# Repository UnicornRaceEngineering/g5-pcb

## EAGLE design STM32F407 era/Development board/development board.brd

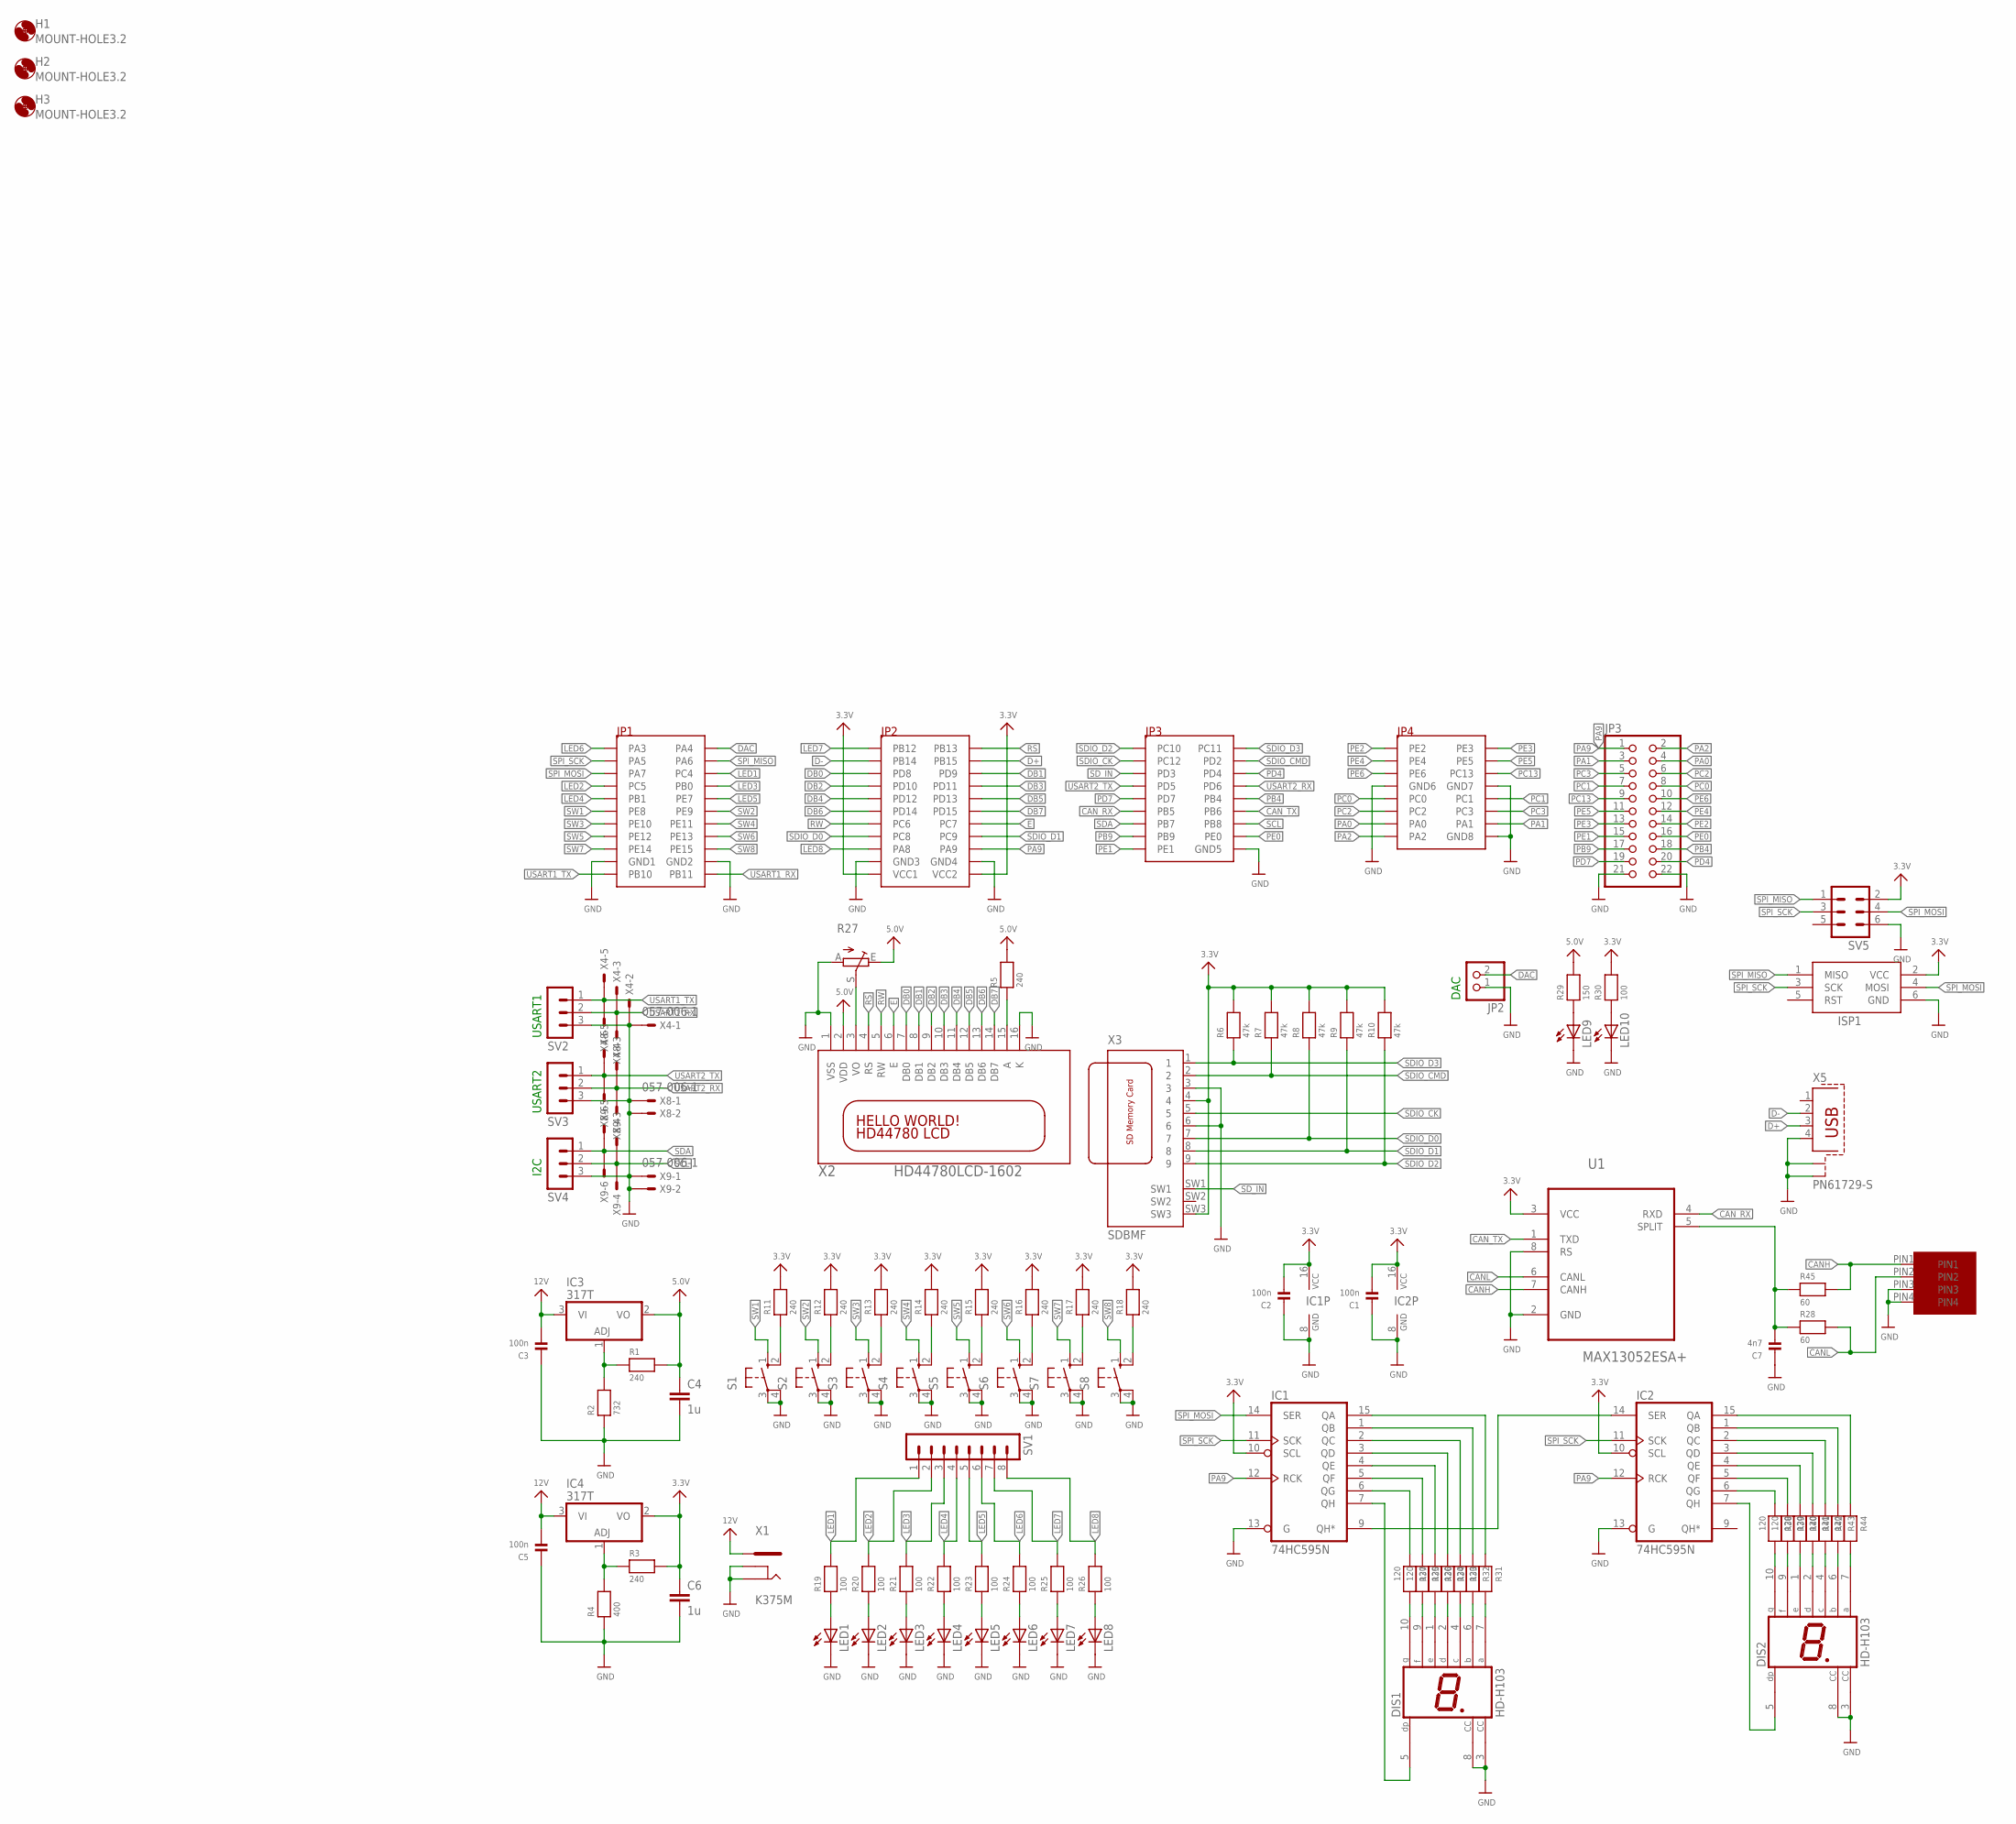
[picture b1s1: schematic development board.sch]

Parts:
C1, C2, C3, C5: 100n; _0603
C4, C6: 1u; C050-035X075
C7: 4n7; _0603
DIS1, DIS2: HD-H103; HDSP-M
H1, H2, H3: MOUNT-HOLE3.2; 3,2
IC1, IC2: 74HC595N; DIL16
IC3, IC4: 317T; TO220H
ISP1: AVRISP-BOX
JP2: HEADER-1X2ROUND; 1X02_ROUND
JP3: PINHD-2X11; 2X11
LED1, LED2, LED3, LED4, LED5, LED6, LED7, LED8: LED5MM
LED9, LED10: LED3MM
R1, R3, R5, R11, R12, R13, R14, R15, R16, R17, R18: 240; _0603
R2: 732; _0603
R4: 400; _0603
R6, R7, R8, R9, R10: 47k; _0603
R19, R20, R21, R22, R23, R24, R25, R26, R30: 100; _0603
R27: TRIM_EU-RJ9W; RJ9W
R28, R45: 60; _0603
R29: 150; _0603
R31, R32, R33, R34, R35, R36, R37, R38, R39, R40, R41, R42, R43, R44: 120; _0603
S1, S2, S3, S4, S5, S6, S7, S8: 10-XX; B3F-10XX
SV1: MA08-1
SV2, SV3, SV4: MA03-1
SV5: MA03-2
U1: MAX13052ESA+; SOIC127P600X175-8N
U$1: CPU-BOARD; CPU-BOARD-JP1
U$57: MICROFIT4; MICROFIT4SOCK
X1: K375M
X2: HD44780LCD-1602; LCD1602
X3: SDBMF; SDBMF-009XXBXX2
X4, X8, X9: 057-006-1
X5: PN61729-S

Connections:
3.3V: C1.2, C2.2, C6.1, IC1.10 (SCL), IC1.16 (VCC), IC2.10 (SCL), IC2.16 (VCC), IC4.2 (VO), ISP1.2 (VCC), R3.2, R6.2, R7.2, R8.2, R9.2, R10.2, R11.2, R12.2, R13.2, R14.2, R15.2, R16.2, R17.2, R18.2, R30.2, SV5.2, U1.3 (VCC), U$1.P$43 (VCC1), U$1.P$44 (VCC2), X3.4, X3.SW3
5.0V: C4.1, IC3.2 (VO), R1.2, R5.2, R27.E, R29.2, X2.2 (VDD)
12V: C3.2, C5.2, IC3.3 (VI), IC4.3 (VI), X1.1
CANH: R45.2, U1.7 (CANH), U$57.PIN1
CANL: R28.2, U1.6 (CANL), U$57.PIN2
CAN_RX: U1.4 (RXD), U$1.P$55 (PB5)
CAN_TX: U1.1 (TXD), U$1.P$56 (PB6)
D+: U$1.P$26 (PB15), X5.3
D-: U$1.P$25 (PB14), X5.2
DAC: JP2.2, U$1.P$2 (PA4)
DB0: U$1.P$27 (PD8), X2.7 (DB0)
DB1: U$1.P$28 (PD9), X2.8 (DB1)
DB2: U$1.P$29 (PD10), X2.9 (DB2)
DB3: U$1.P$30 (PD11), X2.10 (DB3)
DB4: U$1.P$31 (PD12), X2.11 (DB4)
DB5: U$1.P$32 (PD13), X2.12 (DB5)
DB6: U$1.P$33 (PD14), X2.13 (DB6)
DB7: U$1.P$34 (PD15), X2.14 (DB7)
E: U$1.P$36 (PC7), X2.6 (E)
GND: C1.1, C2.1, C3.1, C4.2, C5.1, C6.2, C7.1, DIS1.3 (CC), DIS1.8 (CC), DIS2.3 (CC), DIS2.8 (CC), IC1.8 (GND), IC1.13 (G), IC2.8 (GND), IC2.13 (G), ISP1.6 (GND), JP2.1, JP3.21, JP3.22, LED1.K (C), LED2.K (C), LED3.K (C), LED4.K (C), LED5.K (C), LED6.K (C), LED7.K (C), LED8.K (C), LED9.K (C), LED10.K (C), R2.1, R4.1, R27.A, S1.3, S1.4 (P1), S2.3, S2.4 (P1), S3.3, S3.4 (P1), S4.3, S4.4 (P1), S5.3, S5.4 (P1), S6.3, S6.4 (P1), S7.3, S7.4 (P1), S8.3, S8.4 (P1), SV2.3, SV3.3, SV4.3, SV5.6, U1.2 (GND), U1.8 (RS), U$1.P$21 (GND1), U$1.P$22 (GND2), U$1.P$41 (GND3), U$1.P$42 (GND4), U$1.P$62 (GND5), U$1.P$69 (GND6), U$1.P$70 (GND7), U$1.P$78 (GND8), U$57.PIN3, U$57.PIN4, X1.2, X1.3, X2.1 (VSS), X2.16 (K), X3.3, X3.6, X4.1, X4.2, X5.4, X5.S1, X5.S2, X8.1, X8.2, X9.1, X9.2
LED1: R19.2, SV1.1, U$1.P$6 (PC4)
LED2: R20.2, SV1.2, U$1.P$7 (PC5)
LED3: R21.2, SV1.3, U$1.P$8 (PB0)
LED4: R22.2, SV1.4, U$1.P$9 (PB1)
LED5: R23.2, SV1.5, U$1.P$10 (PE7)
LED6: R24.2, SV1.6, U$1.P$1 (PA3)
LED7: R25.2, SV1.7, U$1.P$23 (PB12)
LED8: R26.2, SV1.8, U$1.P$39 (PA8)
unnamed: DIS2.5 (DP), IC2.7 (QH)
unnamed: IC2.6 (QG), R38.1
unnamed: IC2.5 (QF), R39.1
unnamed: IC2.4 (QE), R40.1
unnamed: IC2.3 (QD), R41.1
unnamed: IC2.2 (QC), R42.1
unnamed: IC2.1 (QB), R43.1
unnamed: IC2.15 (QA), R44.1
unnamed: IC1.9 (QH*), IC2.14 (SER)
unnamed: DIS1.5 (DP), IC1.7 (QH)
unnamed: IC1.6 (QG), R37.1
unnamed: IC1.5 (QF), R35.1
unnamed: IC1.4 (QE), R36.1
unnamed: IC1.3 (QD), R34.1
unnamed: IC1.2 (QC), R33.1
unnamed: IC1.1 (QB), R32.1
unnamed: IC1.15 (QA), R31.1
unnamed: R5.1, X2.15 (A)
unnamed: R11.1, S1.2 (S1)
unnamed: LED10.A, R30.1
unnamed: R12.1, S2.2 (S1)
unnamed: IC3.1 (ADJ), R1.1, R2.2
unnamed: R13.1, S3.2 (S1)
unnamed: IC4.1 (ADJ), R3.1, R4.2
unnamed: R14.1, S4.2 (S1)
unnamed: R15.1, S5.2 (S1)
unnamed: R16.1, S6.2 (S1)
unnamed: R17.1, S7.2 (S1)
unnamed: R18.1, S8.2 (S1)
unnamed: LED1.A, R19.1
unnamed: LED9.A, R29.1
unnamed: LED2.A, R20.1
unnamed: LED3.A, R21.1
unnamed: LED4.A, R22.1
unnamed: LED5.A, R23.1
unnamed: LED6.A, R24.1
unnamed: LED7.A, R25.1
unnamed: LED8.A, R26.1
unnamed: DIS1.7 (A), R31.2
unnamed: DIS1.6 (B), R32.2
unnamed: DIS1.4 (C), R33.2
unnamed: DIS1.2 (D), R34.2
unnamed: DIS1.9 (F), R35.2
unnamed: DIS1.1 (E), R36.2
unnamed: DIS1.10 (G), R37.2
unnamed: DIS2.10 (G), R38.2
unnamed: DIS2.9 (F), R39.2
unnamed: DIS2.1 (E), R40.2
unnamed: DIS2.2 (D), R41.2
unnamed: DIS2.4 (C), R42.2
unnamed: DIS2.6 (B), R43.2
unnamed: DIS2.7 (A), R44.2
unnamed: C7.2, R28.1, R45.1, U1.5 (SPLIT)
PA0: JP3.4, U$1.P$75 (PA0)
PA1: JP3.3, U$1.P$76 (PA1)
PA2: JP3.2, U$1.P$77 (PA2)
PA9: IC1.12 (RCK), IC2.12 (RCK), JP3.1, U$1.P$40 (PA9)
PB4: JP3.18, U$1.P$54 (PB4)
PB9: JP3.17, U$1.P$59 (PB9)
PC0: JP3.8, U$1.P$71 (PC0)
PC1: JP3.7, U$1.P$72 (PC1)
PC2: JP3.6, U$1.P$73 (PC2)
PC3: JP3.5, U$1.P$74 (PC3)
PC13: JP3.9, U$1.P$68 (PC13)
PD4: JP3.20, U$1.P$50 (PD4)
PD7: JP3.19, U$1.P$53 (PD7)
PE0: JP3.16, U$1.P$60 (PE0)
PE1: JP3.15, U$1.P$61 (PE1)
PE2: JP3.14, U$1.P$63 (PE2)
PE3: JP3.13, U$1.P$64 (PE3)
PE4: JP3.12, U$1.P$65 (PE4)
PE5: JP3.11, U$1.P$66 (PE5)
PE6: JP3.10, U$1.P$67 (PE6)
RS: U$1.P$24 (PB13), X2.4 (RS)
RW: U$1.P$35 (PC6), X2.5 (RW)
SCL: SV4.2, U$1.P$58 (PB8), X9.3, X9.4
SDA: SV4.1, U$1.P$57 (PB7), X9.5, X9.6
SDIO_CK: U$1.P$47 (PC12), X3.5
SDIO_CMD: R7.1, U$1.P$48 (PD2), X3.2
SDIO_D0: R8.1, U$1.P$37 (PC8), X3.7
SDIO_D1: R9.1, U$1.P$38 (PC9), X3.8
SDIO_D2: R10.1, U$1.P$45 (PC10), X3.9
SDIO_D3: R6.1, U$1.P$46 (PC11), X3.1
SD_IN: U$1.P$49 (PD3), X3.SW1
SPI_MISO: ISP1.1 (MISO), SV5.1, U$1.P$4 (PA6)
SPI_MOSI: IC1.14 (SER), ISP1.4 (MOSI), SV5.4, U$1.P$5 (PA7)
SPI_SCK: IC1.11 (SCK), IC2.11 (SCK), ISP1.3 (SCK), SV5.3, U$1.P$3 (PA5)
SW1: S1.1 (S), U$1.P$11 (PE8)
SW2: S2.1 (S), U$1.P$12 (PE9)
SW3: S3.1 (S), U$1.P$13 (PE10)
SW4: S4.1 (S), U$1.P$14 (PE11)
SW5: S5.1 (S), U$1.P$15 (PE12)
SW6: S6.1 (S), U$1.P$16 (PE13)
SW7: S7.1 (S), U$1.P$17 (PE14)
SW8: S8.1 (S), U$1.P$18 (PE15)
USART1_RX: SV2.2, U$1.P$20 (PB11), X4.3, X4.4
USART1_TX: SV2.1, U$1.P$19 (PB10), X4.5, X4.6
USART2_RX: SV3.2, U$1.P$52 (PD6), X8.3, X8.4
USART2_TX: SV3.1, U$1.P$51 (PD5), X8.5, X8.6
VO: R27.S, X2.3 (VO)

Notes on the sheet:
USART1
USART2
I2C
DAC

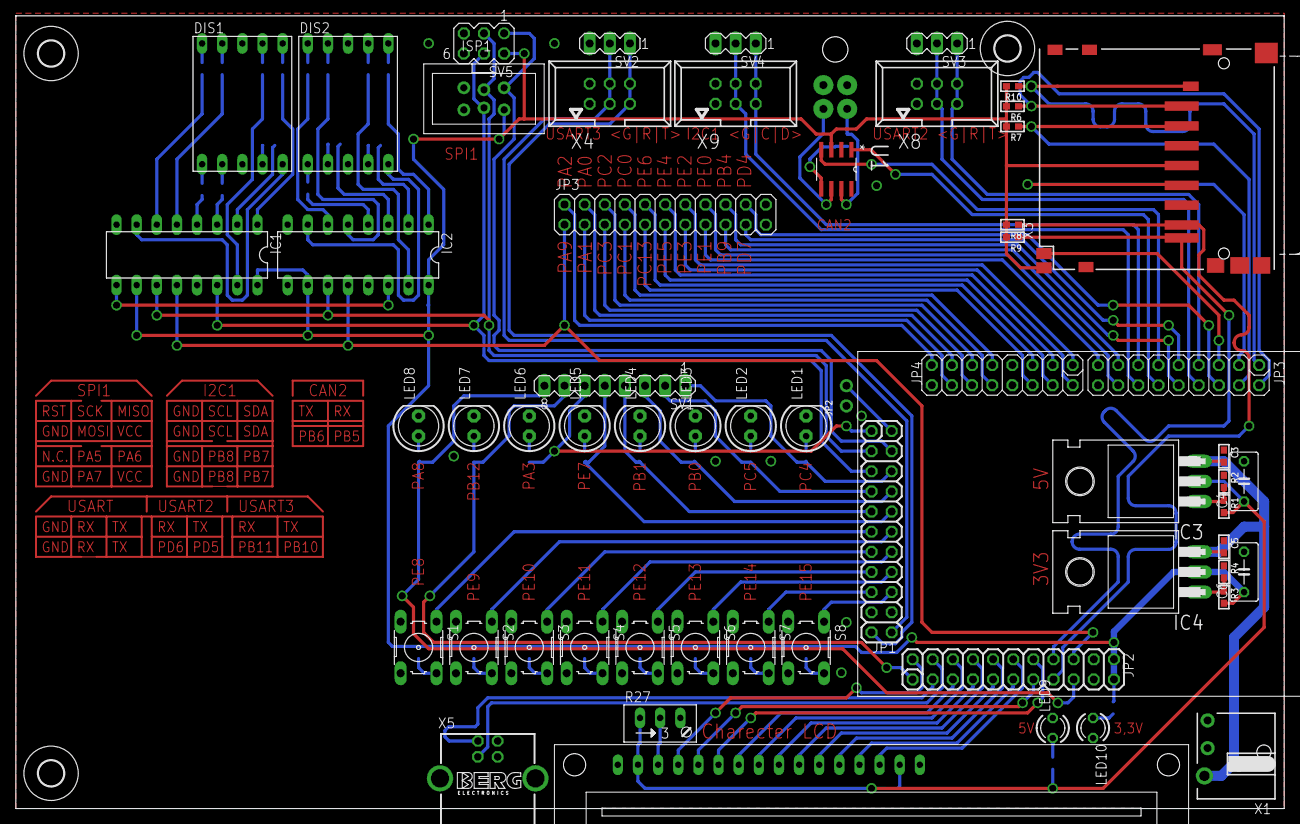
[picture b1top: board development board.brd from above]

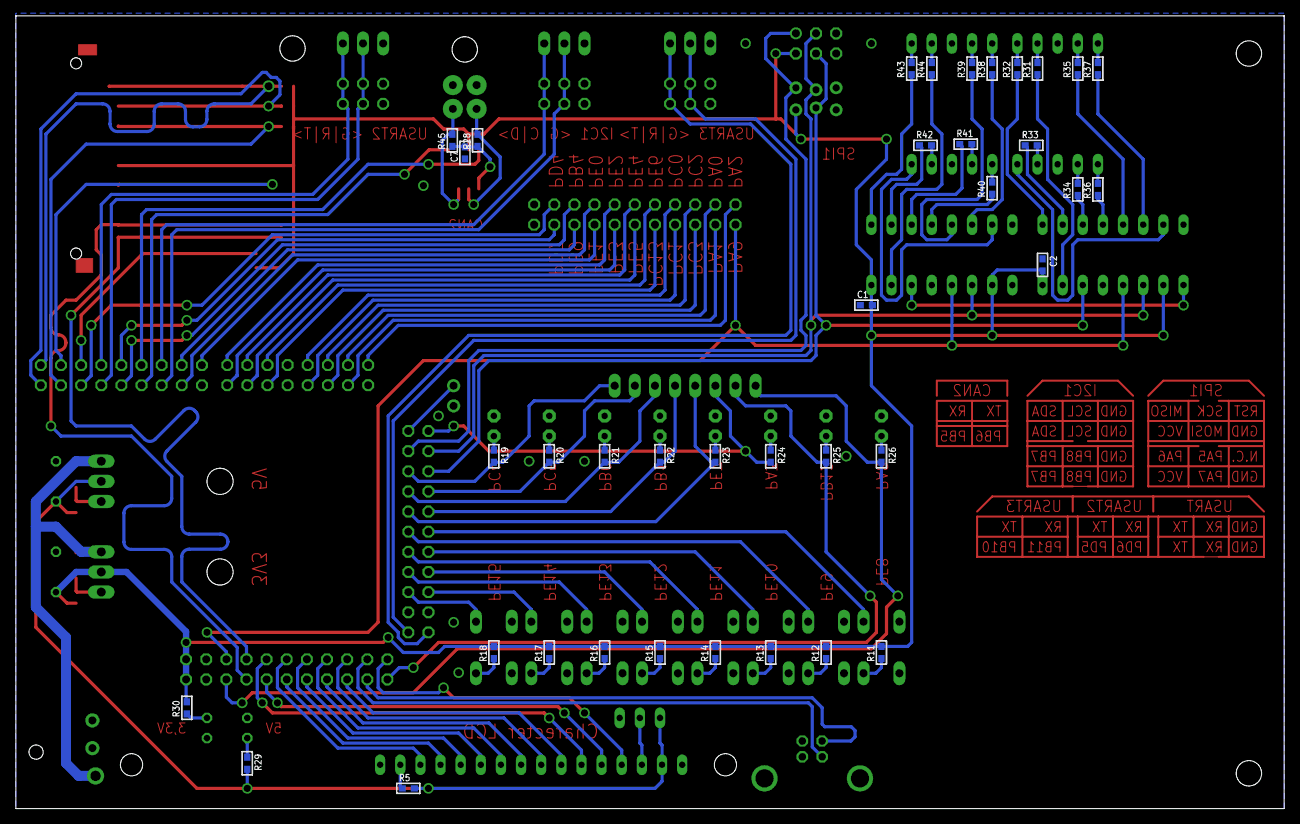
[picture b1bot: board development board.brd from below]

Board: 2 copper layers, 160.0 x 100.0 mm, 97 parts (38 on the bottom side), 128 nets.

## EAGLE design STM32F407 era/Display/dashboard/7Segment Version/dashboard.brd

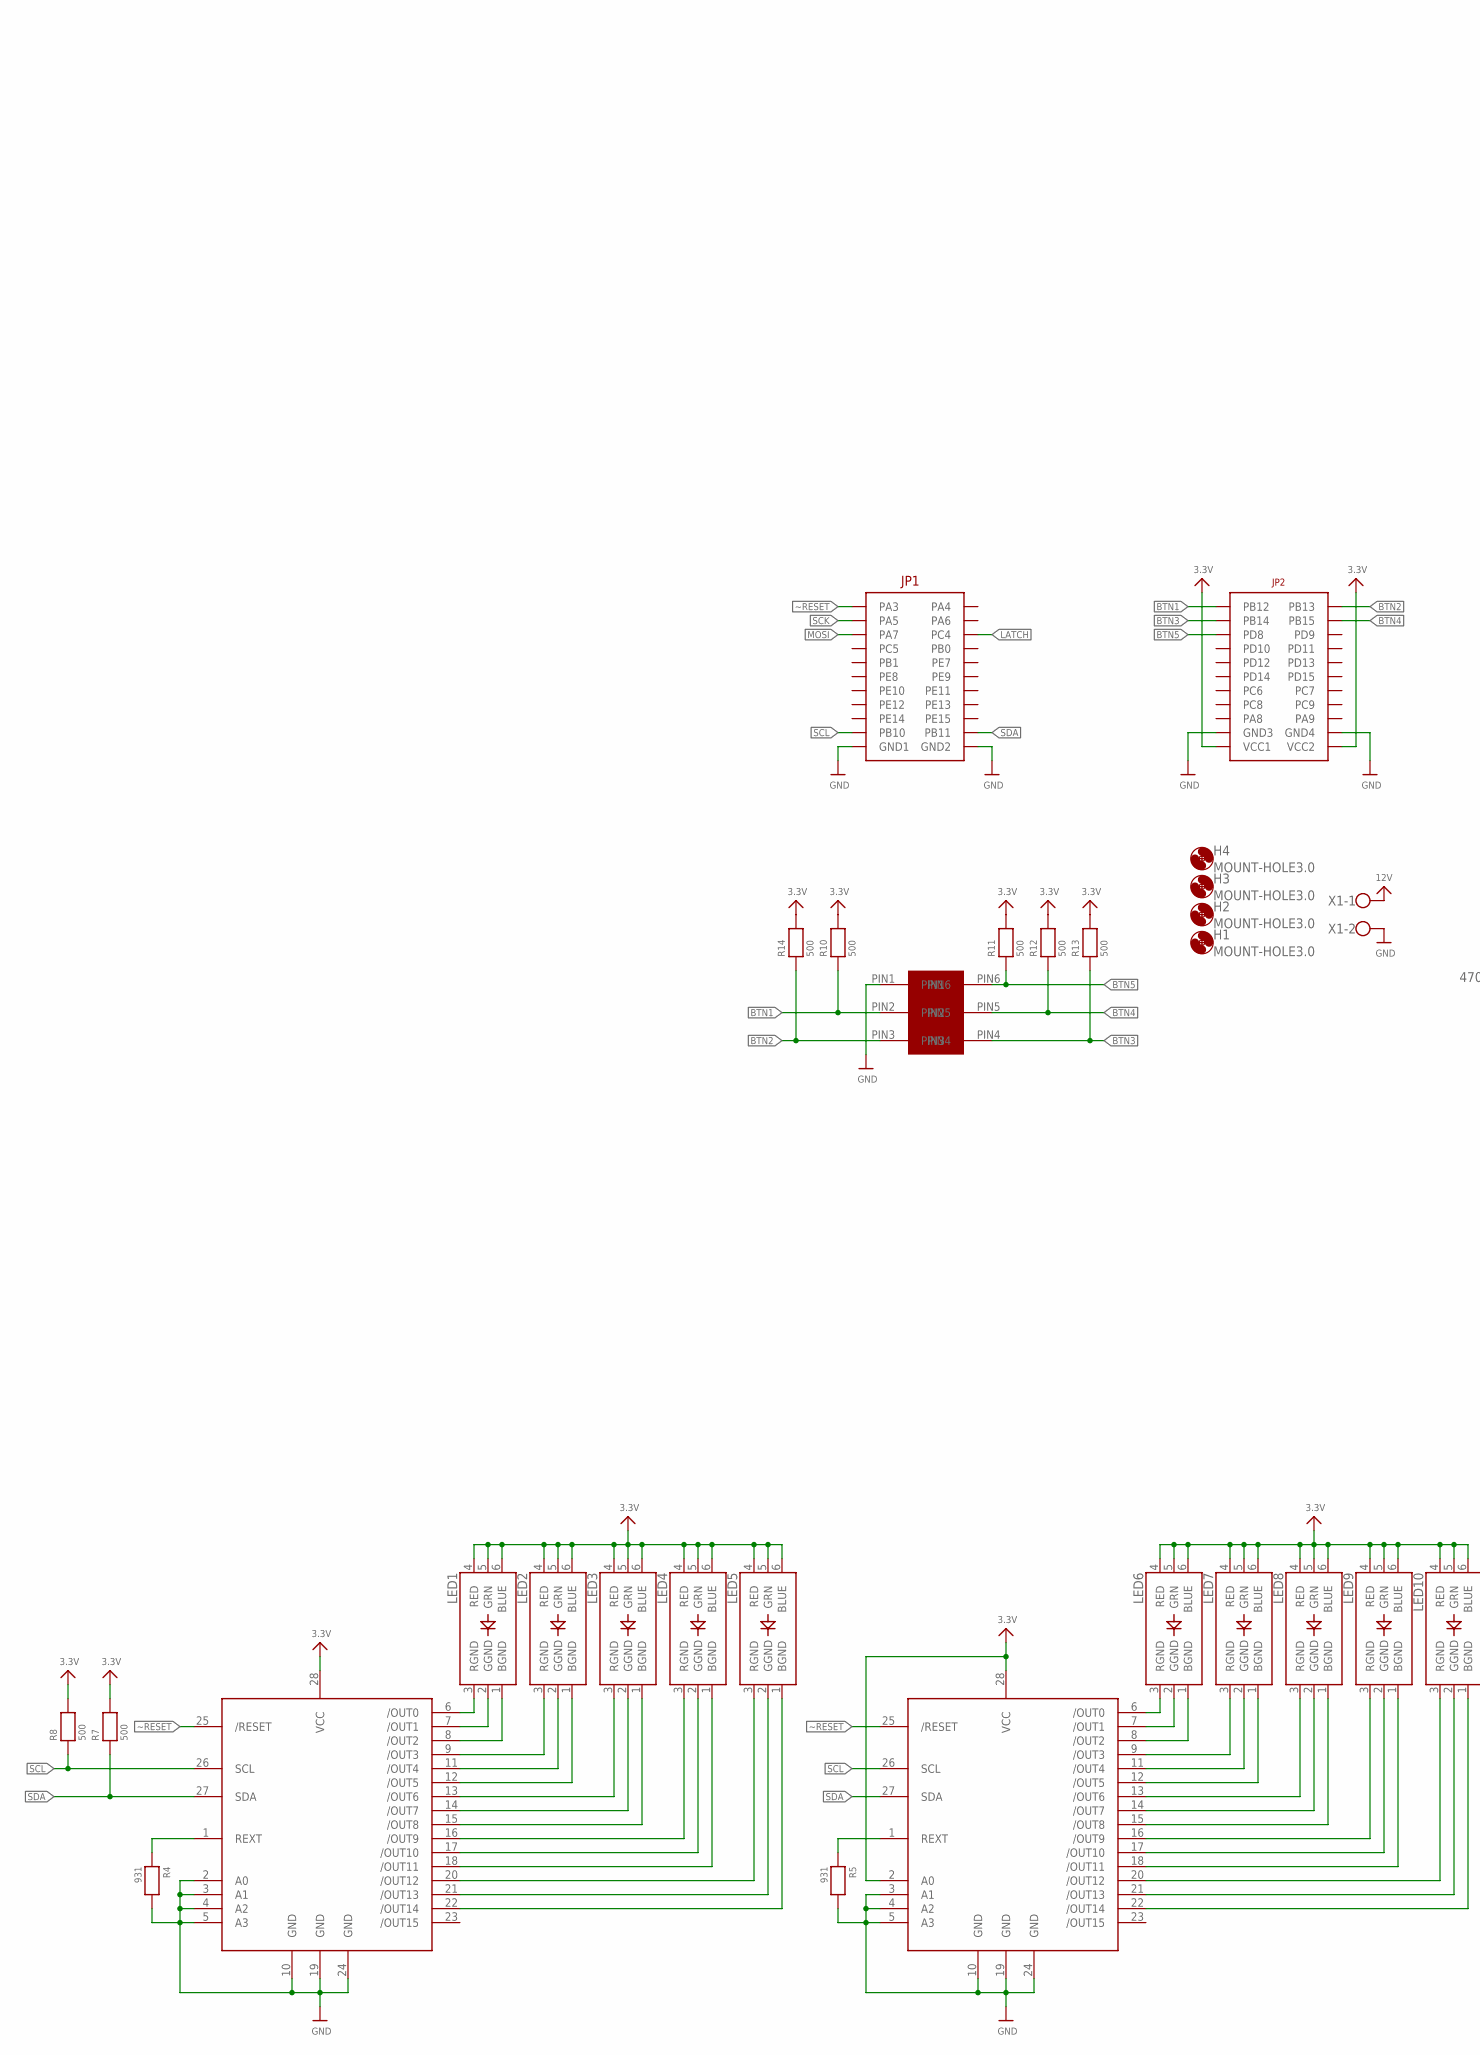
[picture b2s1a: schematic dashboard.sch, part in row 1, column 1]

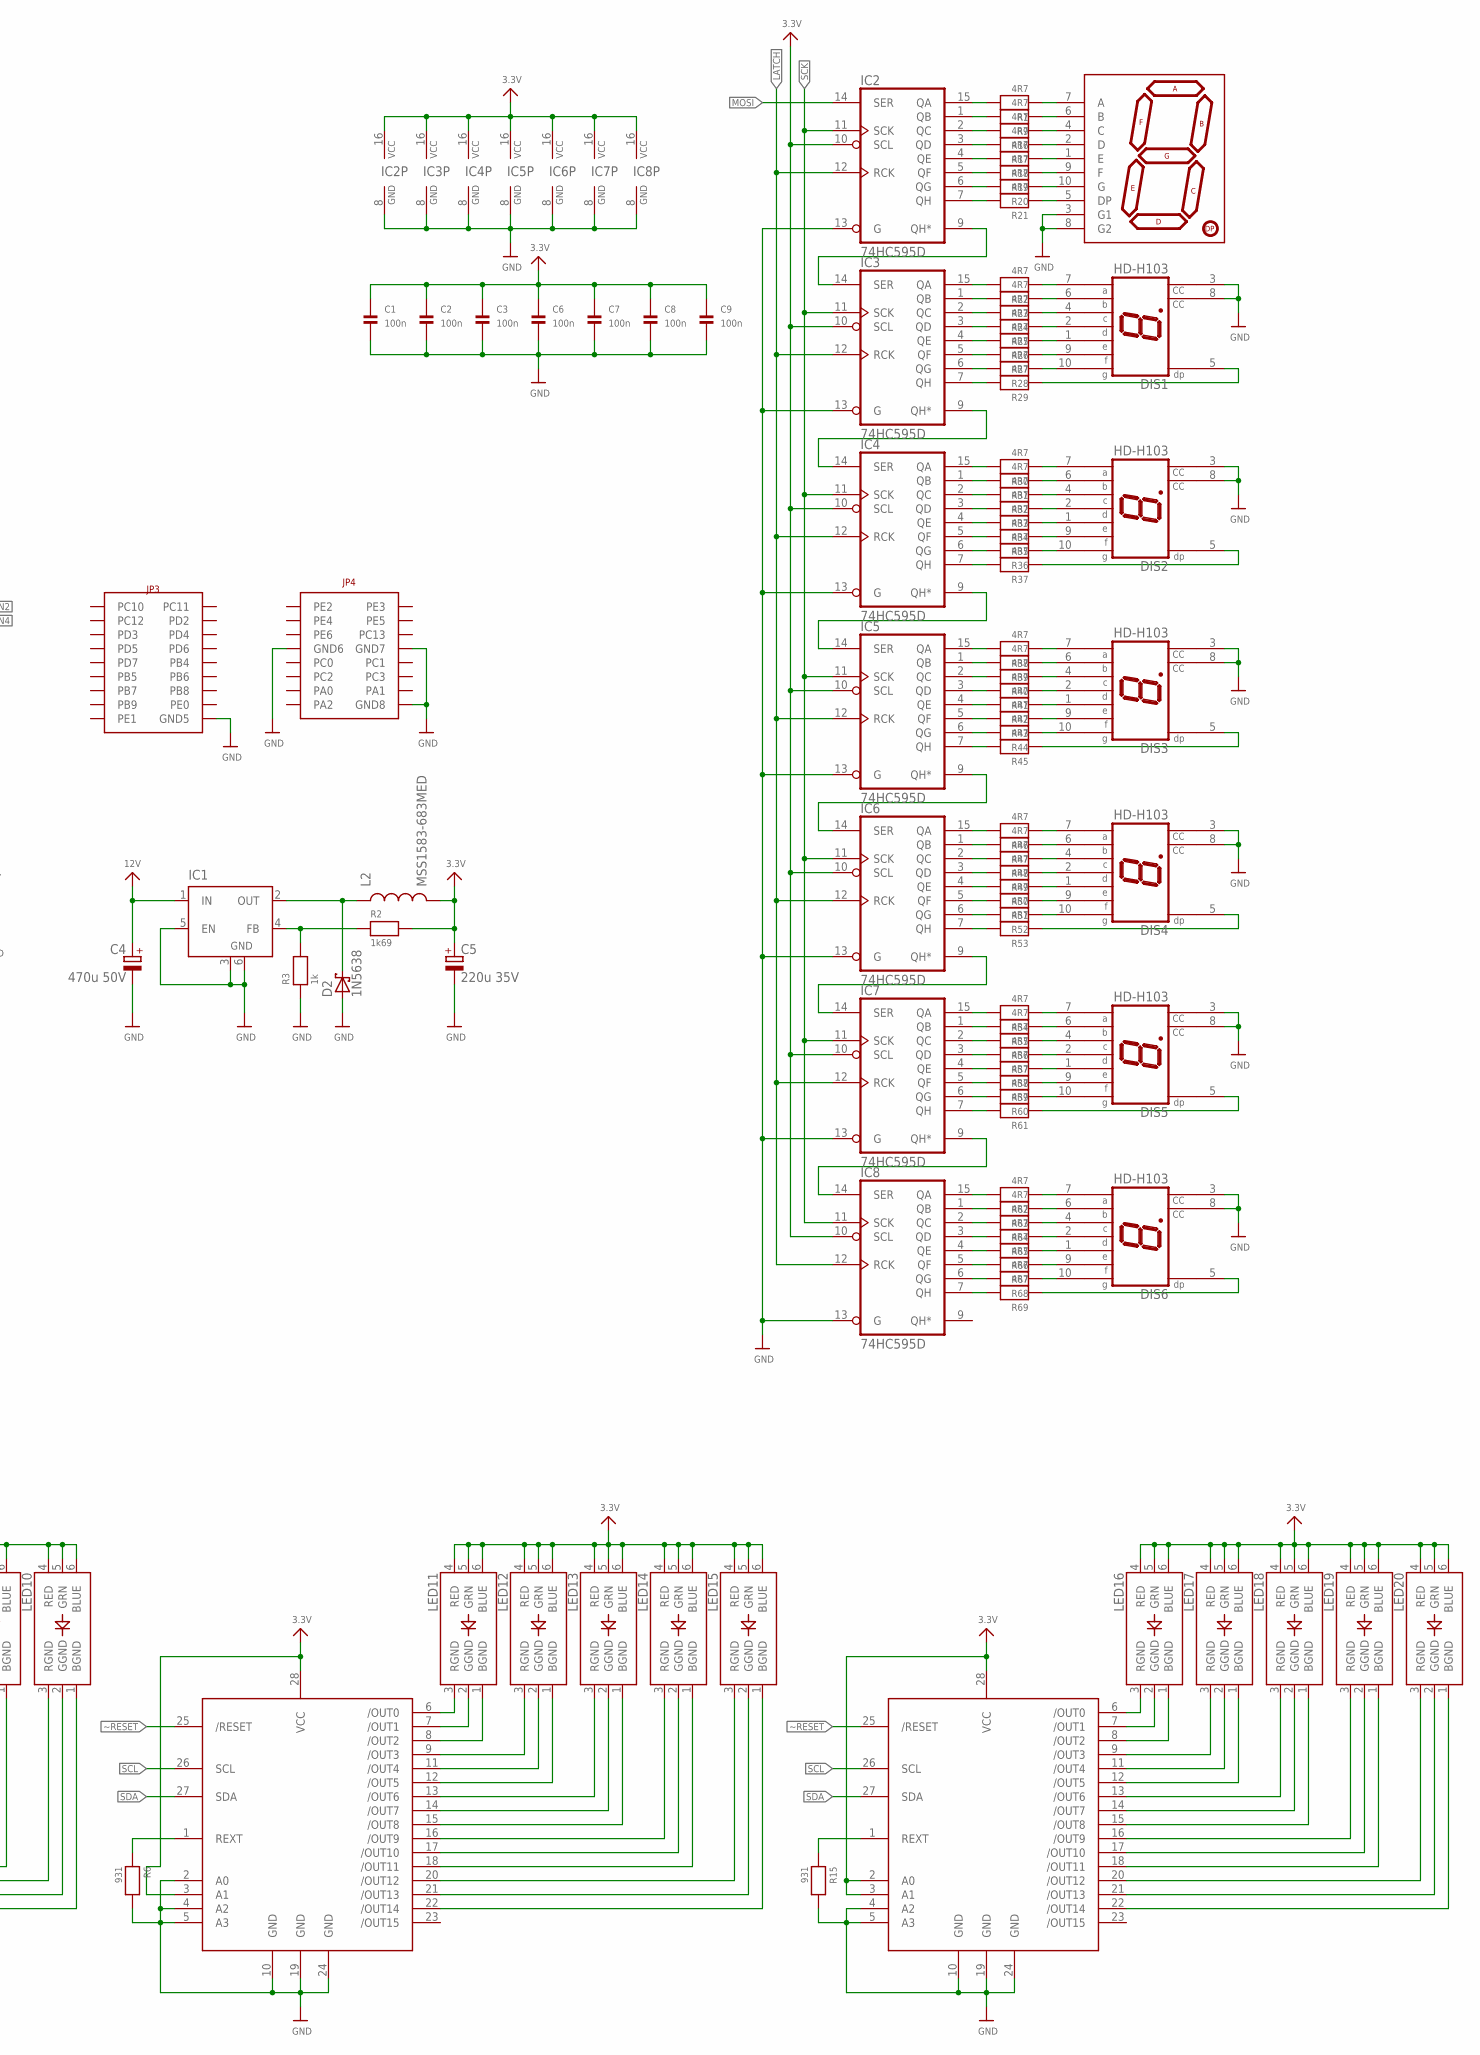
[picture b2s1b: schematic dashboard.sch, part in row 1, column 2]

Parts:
C1, C2, C3, C6, C7, C8, C9: 100n; _0603
C4: 470u 50V; E5-13
C5: 220u 35V; E3,5-8
D2: 1N5638; DO13M
DIS1, DIS2, DIS3, DIS4, DIS5, DIS6: HD-H103; HDSP-M
H1, H2, H3, H4: MOUNT-HOLE3.0; 3,0
IC1: LM2596S; TO263-5
IC2, IC3, IC4, IC5, IC6, IC7, IC8: 74HC595D; SO16
L2: MSS1583-683MED; CDRH125
LED1, LED2, LED3, LED4, LED5, LED6, LED7, LED8, LED9, LED10, LED11, LED12, LED13, LED14, LED15, LED16, LED17, LED18, LED19, LED20: LED_RGB_PLCC6CREE-CLV6A; RGBLED_PLCC6
R1, R9, R16, R17, R18, R19, R20, R21, R22, R23, R24, R25, R26, R27, R28, R29, R30, R31, R32, R33, R34, R35, R36, R37, R38, R39, R40, R41, R42, R43, R44, R45, R46, R47, R48, R49, R50, R51, R52, R53, R54, R55, R56, R57, R58, R59, R60, R61, R62, R63, R64, R65, R66, R67, R68, R69: 4R7; _0603
R2: 1k69; _0603
R3: 1k; _0603
R4, R5, R6, R15: 931; _0603
R7, R8: 500; _0603
R10, R11, R12, R13, R14: 500; _0805
U$1: CPU-BOARD; CPU-BOARD-JP1
U$9: 7-SEGMENT-DISPLAY-1"-RED; 7-SEGMENT-1"PTH
U$30, U$33, U$36, U$51: TLC59116; TSSOP28
U$42: MICROFIT6; MICROFIT6SOCK
X1: W237-102

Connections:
3.3V: C1.1, C2.1, C3.1, C5.+, C6.1, C7.1, C8.1, C9.1, IC2.10 (SCL), IC2.16 (VCC), IC3.10 (SCL), IC3.16 (VCC), IC4.10 (SCL), IC4.16 (VCC), IC5.10 (SCL), IC5.16 (VCC), IC6.10 (SCL), IC6.16 (VCC), IC7.10 (SCL), IC7.16 (VCC), IC8.10 (SCL), IC8.16 (VCC), L2.2, LED1.4 (RED), LED1.5 (GRN), LED1.6 (BLUE), LED2.4 (RED), LED2.5 (GRN), LED2.6 (BLUE), LED3.4 (RED), LED3.5 (GRN), LED3.6 (BLUE), LED4.4 (RED), LED4.5 (GRN), LED4.6 (BLUE), LED5.4 (RED), LED5.5 (GRN), LED5.6 (BLUE), LED6.4 (RED), LED6.5 (GRN), LED6.6 (BLUE), LED7.4 (RED), LED7.5 (GRN), LED7.6 (BLUE), LED8.4 (RED), LED8.5 (GRN), LED8.6 (BLUE), LED9.4 (RED), LED9.5 (GRN), LED9.6 (BLUE), LED10.4 (RED), LED10.5 (GRN), LED10.6 (BLUE), LED11.4 (RED), LED11.5 (GRN), LED11.6 (BLUE), LED12.4 (RED), LED12.5 (GRN), LED12.6 (BLUE), LED13.4 (RED), LED13.5 (GRN), LED13.6 (BLUE), LED14.4 (RED), LED14.5 (GRN), LED14.6 (BLUE), LED15.4 (RED), LED15.5 (GRN), LED15.6 (BLUE), LED16.4 (RED), LED16.5 (GRN), LED16.6 (BLUE), LED17.4 (RED), LED17.5 (GRN), LED17.6 (BLUE), LED18.4 (RED), LED18.5 (GRN), LED18.6 (BLUE), LED19.4 (RED), LED19.5 (GRN), LED19.6 (BLUE), LED20.4 (RED), LED20.5 (GRN), LED20.6 (BLUE), R2.2, R7.2, R8.2, R10.2, R11.2, R12.2, R13.2, R14.2, U$1.P$43 (VCC1), U$1.P$44 (VCC2), U$30.28 (VCC), U$33.2 (A0), U$33.28 (VCC), U$36.3 (A1), U$36.28 (VCC), U$51.2 (A0), U$51.3 (A1), U$51.28 (VCC)
12V: C4.+, IC1.1 (IN), X1.1
BTN1: R10.1, U$1.P$23 (PB12), U$42.PIN2
BTN2: R14.1, U$1.P$24 (PB13), U$42.PIN3
BTN3: R13.1, U$1.P$25 (PB14), U$42.PIN4
BTN4: R12.1, U$1.P$26 (PB15), U$42.PIN5
BTN5: R11.1, U$1.P$27 (PD8), U$42.PIN6
GND: C1.2, C2.2, C3.2, C4.-, C5.-, C6.2, C7.2, C8.2, C9.2, D2.A, DIS1.3 (CC), DIS1.8 (CC), DIS2.3 (CC), DIS2.8 (CC), DIS3.3 (CC), DIS3.8 (CC), DIS4.3 (CC), DIS4.8 (CC), DIS5.3 (CC), DIS5.8 (CC), DIS6.3 (CC), DIS6.8 (CC), IC1.3 (GND), IC1.5 (EN), IC1.6 (GND), IC2.8 (GND), IC2.13 (G), IC3.8 (GND), IC3.13 (G), IC4.8 (GND), IC4.13 (G), IC5.8 (GND), IC5.13 (G), IC6.8 (GND), IC6.13 (G), IC7.8 (GND), IC7.13 (G), IC8.8 (GND), IC8.13 (G), R3.1, R4.2, R5.2, R6.2, R15.2, U$1.P$21 (GND1), U$1.P$22 (GND2), U$1.P$41 (GND3), U$1.P$42 (GND4), U$1.P$62 (GND5), U$1.P$69 (GND6), U$1.P$70 (GND7), U$1.P$78 (GND8), U$9.3 (G1), U$9.8 (G2), U$30.2 (A0), U$30.3 (A1), U$30.4 (A2), U$30.5 (A3), U$30.10 (GND), U$30.19 (GND), U$30.24 (GND), U$33.3 (A1), U$33.4 (A2), U$33.5 (A3), U$33.10 (GND), U$33.19 (GND), U$33.24 (GND), U$36.2 (A0), U$36.4 (A2), U$36.5 (A3), U$36.10 (GND), U$36.19 (GND), U$36.24 (GND), U$42.PIN1, U$51.4 (A2), U$51.5 (A3), U$51.10 (GND), U$51.19 (GND), U$51.24 (GND), X1.2
LATCH: IC2.12 (RCK), IC3.12 (RCK), IC4.12 (RCK), IC5.12 (RCK), IC6.12 (RCK), IC7.12 (RCK), IC8.12 (RCK), U$1.P$6 (PC4)
MOSI: IC2.14 (SER), U$1.P$5 (PA7)
unnamed: IC2.15 (QA), R1.2
unnamed: IC2.1 (QB), R9.2
unnamed: IC2.2 (QC), R16.2
unnamed: IC2.3 (QD), R17.2
unnamed: IC2.4 (QE), R18.2
unnamed: IC1.4 (FB), R2.1, R3.2
unnamed: LED1.3 (RGND), U$30.6 (/OUT0)
unnamed: LED1.2 (GGND), U$30.7 (/OUT1)
unnamed: D2.C, IC1.2 (OUT), L2.1
unnamed: LED1.1 (BGND), U$30.8 (/OUT2)
unnamed: LED2.3 (RGND), U$30.9 (/OUT3)
unnamed: LED2.2 (GGND), U$30.11 (/OUT4)
unnamed: LED2.1 (BGND), U$30.12 (/OUT5)
unnamed: LED3.3 (RGND), U$30.13 (/OUT6)
unnamed: LED3.2 (GGND), U$30.14 (/OUT7)
unnamed: LED3.1 (BGND), U$30.15 (/OUT8)
unnamed: LED4.3 (RGND), U$30.16 (/OUT9)
unnamed: LED4.2 (GGND), U$30.17 (/OUT10)
unnamed: LED4.1 (BGND), U$30.18 (/OUT11)
unnamed: LED5.3 (RGND), U$30.20 (/OUT12)
unnamed: LED5.2 (GGND), U$30.21 (/OUT13)
unnamed: LED5.1 (BGND), U$30.22 (/OUT14)
unnamed: LED6.3 (RGND), U$33.6 (/OUT0)
unnamed: LED6.2 (GGND), U$33.7 (/OUT1)
unnamed: LED6.1 (BGND), U$33.8 (/OUT2)
unnamed: LED7.3 (RGND), U$33.9 (/OUT3)
unnamed: LED7.2 (GGND), U$33.11 (/OUT4)
unnamed: LED7.1 (BGND), U$33.12 (/OUT5)
unnamed: LED8.3 (RGND), U$33.13 (/OUT6)
unnamed: LED8.2 (GGND), U$33.14 (/OUT7)
unnamed: LED8.1 (BGND), U$33.15 (/OUT8)
unnamed: LED9.3 (RGND), U$33.16 (/OUT9)
unnamed: LED9.2 (GGND), U$33.17 (/OUT10)
unnamed: LED9.1 (BGND), U$33.18 (/OUT11)
unnamed: LED10.3 (RGND), U$33.20 (/OUT12)
unnamed: LED10.2 (GGND), U$33.21 (/OUT13)
unnamed: LED10.1 (BGND), U$33.22 (/OUT14)
unnamed: LED11.3 (RGND), U$36.6 (/OUT0)
unnamed: LED11.2 (GGND), U$36.7 (/OUT1)
unnamed: LED11.1 (BGND), U$36.8 (/OUT2)
unnamed: LED12.3 (RGND), U$36.9 (/OUT3)
unnamed: LED12.2 (GGND), U$36.11 (/OUT4)
unnamed: LED12.1 (BGND), U$36.12 (/OUT5)
unnamed: LED13.3 (RGND), U$36.13 (/OUT6)
unnamed: LED13.2 (GGND), U$36.14 (/OUT7)
unnamed: LED13.1 (BGND), U$36.15 (/OUT8)
unnamed: LED14.3 (RGND), U$36.16 (/OUT9)
unnamed: LED14.2 (GGND), U$36.17 (/OUT10)
unnamed: LED14.1 (BGND), U$36.18 (/OUT11)
unnamed: LED15.3 (RGND), U$36.20 (/OUT12)
unnamed: LED15.2 (GGND), U$36.21 (/OUT13)
unnamed: LED15.1 (BGND), U$36.22 (/OUT14)
unnamed: R4.1, U$30.1 (REXT)
unnamed: LED16.3 (RGND), U$51.6 (/OUT0)
unnamed: R5.1, U$33.1 (REXT)
unnamed: R6.1, U$36.1 (REXT)
unnamed: IC2.5 (QF), R19.2
unnamed: IC2.6 (QG), R20.2
unnamed: R1.1, U$9.7 (A)
unnamed: R9.1, U$9.6 (B)
unnamed: R16.1, U$9.4 (C)
unnamed: LED16.2 (GGND), U$51.7 (/OUT1)
unnamed: LED16.1 (BGND), U$51.8 (/OUT2)
unnamed: LED17.3 (RGND), U$51.9 (/OUT3)
unnamed: LED17.2 (GGND), U$51.11 (/OUT4)
unnamed: LED17.1 (BGND), U$51.12 (/OUT5)
unnamed: LED18.3 (RGND), U$51.13 (/OUT6)
unnamed: LED18.2 (GGND), U$51.14 (/OUT7)
unnamed: LED18.1 (BGND), U$51.15 (/OUT8)
unnamed: LED19.3 (RGND), U$51.16 (/OUT9)
unnamed: LED19.2 (GGND), U$51.17 (/OUT10)
unnamed: LED19.1 (BGND), U$51.18 (/OUT11)
unnamed: LED20.3 (RGND), U$51.20 (/OUT12)
unnamed: LED20.2 (GGND), U$51.21 (/OUT13)
unnamed: LED20.1 (BGND), U$51.22 (/OUT14)
unnamed: R15.1, U$51.1 (REXT)
unnamed: R17.1, U$9.2 (D)
unnamed: R18.1, U$9.1 (E)
unnamed: R19.1, U$9.9 (F)
unnamed: R20.1, U$9.10 (G)
unnamed: R21.1, U$9.5 (DP)
unnamed: IC2.7 (QH), R21.2
unnamed: IC3.15 (QA), R22.2
unnamed: IC3.1 (QB), R23.2
unnamed: IC3.2 (QC), R24.2
unnamed: IC3.3 (QD), R25.2
unnamed: IC3.4 (QE), R26.2
unnamed: IC3.5 (QF), R27.2
unnamed: IC3.6 (QG), R28.2
unnamed: IC3.7 (QH), R29.2
unnamed: DIS1.7 (A), R22.1
unnamed: DIS1.6 (B), R23.1
unnamed: DIS1.4 (C), R24.1
unnamed: DIS1.2 (D), R25.1
unnamed: DIS1.1 (E), R26.1
unnamed: DIS1.9 (F), R27.1
unnamed: DIS1.10 (G), R28.1
unnamed: IC4.15 (QA), R30.2
unnamed: IC4.1 (QB), R31.2
unnamed: IC4.2 (QC), R32.2
unnamed: IC4.3 (QD), R33.2
unnamed: IC4.4 (QE), R34.2
unnamed: IC4.5 (QF), R35.2
unnamed: IC4.6 (QG), R36.2
unnamed: IC4.7 (QH), R37.2
unnamed: DIS2.7 (A), R30.1
unnamed: DIS2.6 (B), R31.1
unnamed: DIS2.4 (C), R32.1
unnamed: DIS2.2 (D), R33.1
unnamed: DIS2.1 (E), R34.1
unnamed: DIS2.9 (F), R35.1
unnamed: DIS2.10 (G), R36.1
unnamed: DIS3.7 (A), R38.1
unnamed: DIS3.6 (B), R39.1
unnamed: DIS3.4 (C), R40.1
unnamed: DIS3.2 (D), R41.1
unnamed: DIS3.1 (E), R42.1
unnamed: DIS3.9 (F), R43.1
unnamed: DIS3.10 (G), R44.1
unnamed: IC5.15 (QA), R38.2
unnamed: IC5.1 (QB), R39.2
unnamed: IC5.2 (QC), R40.2
unnamed: IC5.3 (QD), R41.2
unnamed: IC5.4 (QE), R42.2
unnamed: IC5.5 (QF), R43.2
unnamed: IC5.6 (QG), R44.2
unnamed: IC5.7 (QH), R45.2
unnamed: IC6.15 (QA), R46.2
unnamed: IC6.1 (QB), R47.2
unnamed: IC6.2 (QC), R48.2
unnamed: IC6.3 (QD), R49.2
unnamed: IC6.4 (QE), R50.2
unnamed: IC6.5 (QF), R51.2
unnamed: IC6.6 (QG), R52.2
unnamed: IC6.7 (QH), R53.2
unnamed: DIS4.7 (A), R46.1
unnamed: DIS4.6 (B), R47.1
unnamed: DIS4.4 (C), R48.1
unnamed: DIS4.2 (D), R49.1
unnamed: DIS4.1 (E), R50.1
unnamed: DIS4.9 (F), R51.1
unnamed: DIS4.10 (G), R52.1
unnamed: IC7.15 (QA), R54.2
unnamed: IC7.1 (QB), R55.2
unnamed: IC7.2 (QC), R56.2
unnamed: IC7.3 (QD), R57.2
unnamed: IC7.4 (QE), R58.2
unnamed: IC7.5 (QF), R59.2
unnamed: IC7.6 (QG), R60.2
unnamed: IC7.7 (QH), R61.2
unnamed: DIS5.7 (A), R54.1
unnamed: DIS5.6 (B), R55.1
unnamed: DIS5.4 (C), R56.1
unnamed: DIS5.2 (D), R57.1
unnamed: DIS5.1 (E), R58.1
unnamed: DIS5.9 (F), R59.1
unnamed: DIS5.10 (G), R60.1
unnamed: IC8.15 (QA), R62.2
unnamed: IC8.1 (QB), R63.2
unnamed: IC8.2 (QC), R64.2
unnamed: IC8.3 (QD), R65.2
unnamed: IC8.4 (QE), R66.2
unnamed: IC8.5 (QF), R67.2
unnamed: IC8.6 (QG), R68.2
unnamed: IC8.7 (QH), R69.2
unnamed: DIS6.7 (A), R62.1
unnamed: DIS6.6 (B), R63.1
unnamed: DIS6.4 (C), R64.1
unnamed: DIS6.2 (D), R65.1
unnamed: DIS6.1 (E), R66.1
unnamed: DIS6.9 (F), R67.1
unnamed: DIS6.10 (G), R68.1
unnamed: IC2.9 (QH*), IC3.14 (SER)
unnamed: DIS1.5 (DP), R29.1
unnamed: DIS2.5 (DP), R37.1
unnamed: DIS3.5 (DP), R45.1
unnamed: DIS4.5 (DP), R53.1
unnamed: DIS5.5 (DP), R61.1
unnamed: DIS6.5 (DP), R69.1
unnamed: IC3.9 (QH*), IC4.14 (SER)
unnamed: IC4.9 (QH*), IC5.14 (SER)
unnamed: IC5.9 (QH*), IC6.14 (SER)
unnamed: IC6.9 (QH*), IC7.14 (SER)
unnamed: IC7.9 (QH*), IC8.14 (SER)
SCK: IC2.11 (SCK), IC3.11 (SCK), IC4.11 (SCK), IC5.11 (SCK), IC6.11 (SCK), IC7.11 (SCK), IC8.11 (SCK), U$1.P$3 (PA5)
SCL: R8.1, U$1.P$19 (PB10), U$30.26 (SCL), U$33.26 (SCL), U$36.26 (SCL), U$51.26 (SCL)
SDA: R7.1, U$1.P$20 (PB11), U$30.27 (SDA), U$33.27 (SDA), U$36.27 (SDA), U$51.27 (SDA)
~RESET: U$1.P$1 (PA3), U$30.25 (/RESET), U$33.25 (/RESET), U$36.25 (/RESET), U$51.25 (/RESET)

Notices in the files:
parts and their libraries:
SparkFun-Passives: Licensing: Creative Commons ShareAlike 4.0 International - https://creativecommons.org/licenses/by-sa/4.0
microbuilder: This work is placed in the public domain, and may be freely used for commercial and non-commercial work with the following conditions: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
